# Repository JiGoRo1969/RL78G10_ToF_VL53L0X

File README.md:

# VL53L0X(STMicro) ToF sensor with RL78/G10 software library (Rev.20200416)

This is a project to use VL53L0X ToF sensor with RL78/G10
included with CS+ environment setting files provided by Renesas Electronics Corp.
So you can easily modify and add this codes with CS+ on Windows PC.
  
Let's enjoy it !

## Information for target board

RL78/G10 board "AE-R5F10Y47ASP" is provided by Akizukidenshi in Japan.
  
Akizuki : http://akizukidenshi.com/catalog/g/gK-09035/

ToF sensor board is "AE-VL53L0X" by Akizukidenshi or "#15310" by Strawberry Linux
  
Akizuki : http://akizukidenshi.com/catalog/g/gM-12590/

Strawberry Linux : https://strawberry-linux.com/catalog/items?code=15310

## Installation

Import this project into CS+.

## Usage

The protocol stack is defined with an ICS3.5 provided by KONDO Kagaku.
ICS3.5 uses "Data=8bit, Stop=1bit, Parity=EVEN, baudrate=1.5Mbps."
You will get 4 sensor unit data when master MCU/MPU send 4 bytes data as follows :

|Command|SC|Address|Length|
|-------|--|-------|------|
|0xA0+ID|0x7F|0(fiexed)|2(fiexed)|
  
ID is defined as D_MY_ID in "cg_src/r_cg_userdefine.h".

## Current Support Peripherals

|Function Name        | Pin Name        | notes |
|:--------------------|:---------------:|:------|
|I2C I/F              |P06/SCLA0        | connecting to ToF sensor | 
|I2C I/F              |P07/SDAA0        | connecting to ToF sensor | 
|UART I/F             |P00/TxD0         | connecting to RxD of master MCU/MPU | 
|UART I/F             |P01/RxD0         | connecting to TxD of master MCU/MPU | 
|X'tal                |X1,X2            | mounted on board |
|OCD Debugger I/F     |RESET, TOOL0     | connecting to DEBUGGER |
|Non Connections      |P02-05, P41, P137 | |
  
You can refer CAD data with Eagle(.brd and .sch) to understand the circuit.
  
|File Name | purpose |
|:--------:|:-------:|
|RL78G10_ToF_A2.brd| PCB pattern data for ToF sensor with R5F10Y47ASP|
|RL78G10_ToF_A2.sch| circuit data |
|--------|-------|
|RL78G10_E1.brd| PCB pattern data connecting to E1/E2/E2Lite |
|RL78G10_E1.sch| circuit data |

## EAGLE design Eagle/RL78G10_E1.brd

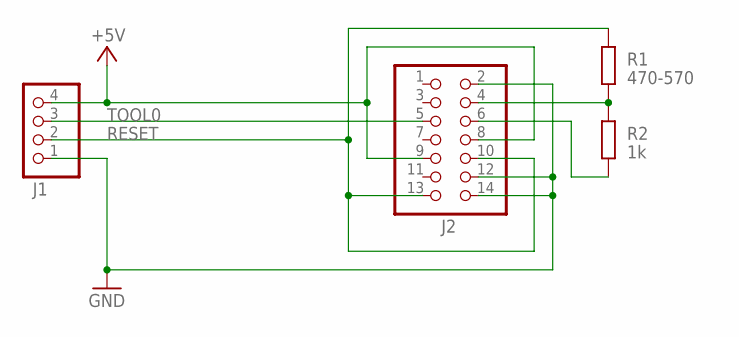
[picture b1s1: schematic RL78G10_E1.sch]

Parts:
J1: PINHD_1X4; PINHD_1X04
J2: PINHD_2X07
R1: 470-570; R0603
R2: 1k; R0603

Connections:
+5V: J1.4, J2.8, J2.9
GND: J1.1, J2.2, J2.12, J2.14
P4: J2.4, R1.1, R2.2
P6: J2.6, R2.1
RESET: J1.2, J2.10, J2.13, R1.2
TOOL0: J1.3, J2.5

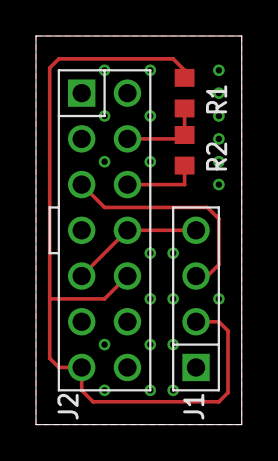
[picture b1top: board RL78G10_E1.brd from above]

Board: 2 copper layers, 11.4 x 21.6 mm, 4 parts (0 on the bottom side), 6 nets.

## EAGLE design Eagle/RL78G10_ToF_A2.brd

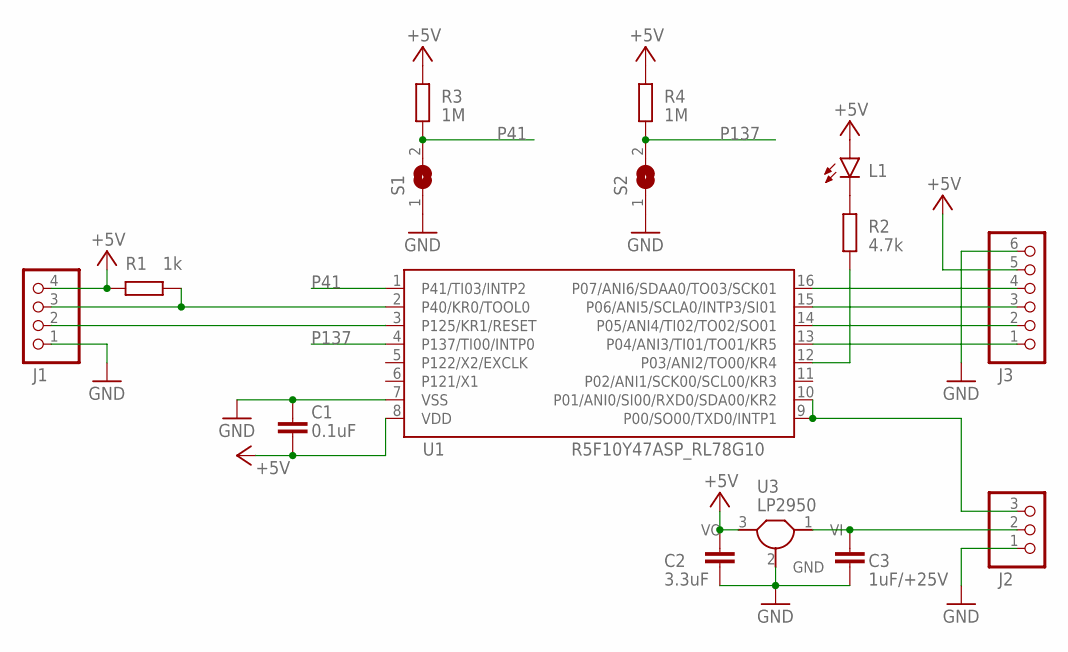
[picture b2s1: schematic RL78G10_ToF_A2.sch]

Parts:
C1: 0.1uF; C0603
C2: 3.3uF; C0805
C3: 1uF/+25V; C0805
J1: PINHD_1X4; PINHD_1X04
J2: PINHD_1X3; PINHD_1X03
J3: PINHD_1X6; PINHD_1X06
L1: LEDSML0603; SML0603
R1: 1k; R0603
R2: 4.7k; R0603
R3, R4: 1M; R0603
S1, S2: SJ-OMINI; SJ-O
U1: R5F10Y47ASP_RL78G10; SSOP16
U3: LP2950; TO92-

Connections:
+5V: C1.2, C2.1, J1.4, J3.5, L1.A, R1.1, R3.1, R4.1, U1.8 (VDD), U3.3 (VO)
+V: C3.1, J2.2, U3.1 (VI)
GND: C1.1, C2.2, C3.2, J1.1, J2.1, J3.6, S1.1, S2.1, U1.7 (VSS), U3.2 (GND)
GPIO1: J3.1, U1.13 (P04/ANI3/TI01/TO01/KR5)
unnamed: L1.C, R2.1
P41: R3.2, S1.2, U1.1 (P41/TI03/INTP2)
P137: R4.2, S2.2, U1.4 (P137/TI00/INTP0)
RESET: J1.2, U1.3 (P125/KR1/RESET)
SCL: J3.3, U1.15 (P06/ANI5/SCLA0/INTP3/SI01)
SDA: J3.4, U1.16 (P07/ANI6/SDAA0/TO03/SCK01)
SHUT: J3.2, U1.14 (P05/ANI4/TI02/TO02/SO01)
SIG: J2.3, U1.9 (P00/SO00/TXD0/INTP1), U1.10 (P01/ANI0/SI00/RXD0/SDA00/KR2)
TO00: R2.2, U1.12 (P03/ANI2/TO00/KR4)
TOOL0: J1.3, R1.2, U1.2 (P40/KR0/TOOL0)

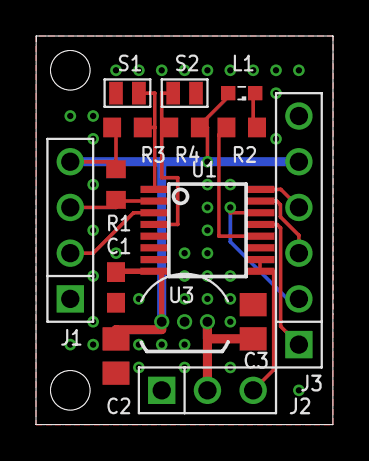
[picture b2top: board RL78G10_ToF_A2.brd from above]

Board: 2 copper layers, 16.5 x 21.6 mm, 15 parts (0 on the bottom side), 14 nets.

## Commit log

2020-05-14 Rev.20200416
2020-06-17 Rev.20200416 with Eagle
